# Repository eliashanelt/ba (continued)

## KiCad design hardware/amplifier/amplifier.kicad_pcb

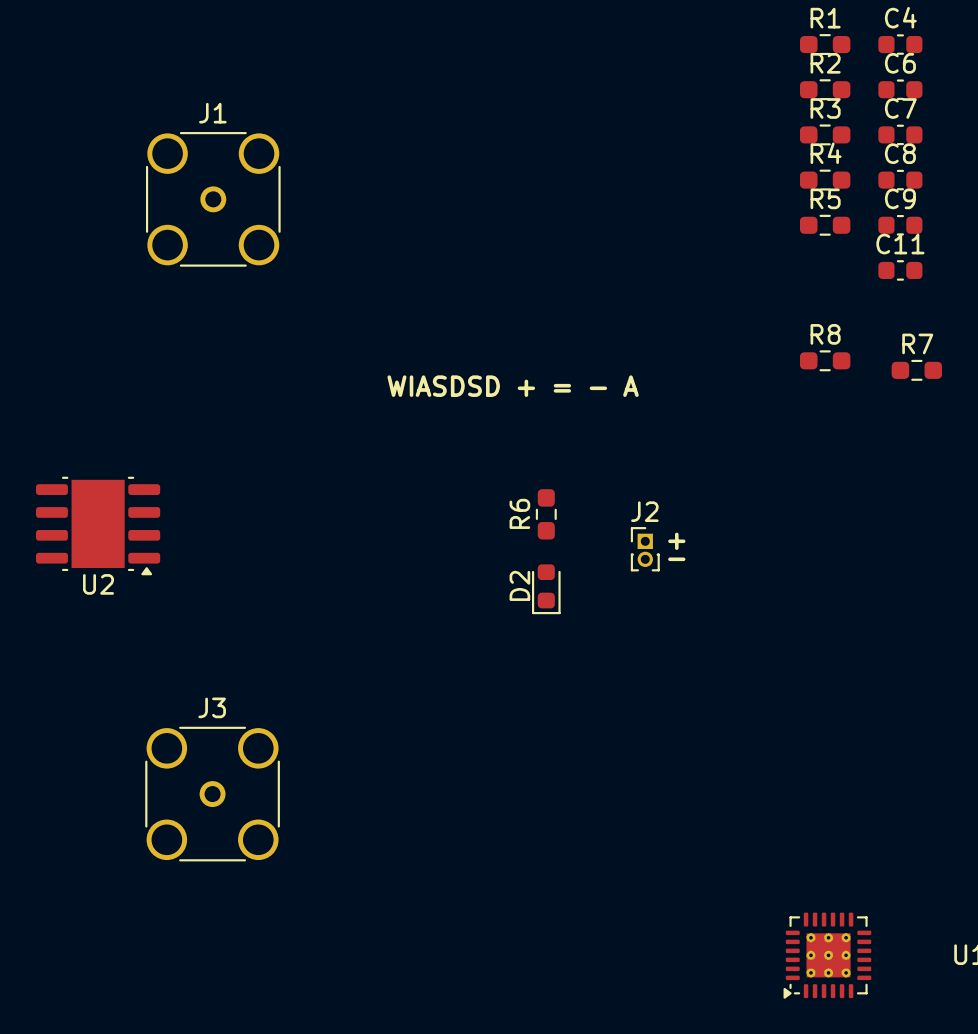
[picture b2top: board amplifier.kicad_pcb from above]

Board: 2 copper layers, 20 parts (0 on the bottom side), 16 nets, no tracks yet.

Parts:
C4, C9: 4.7nF; C_0603_1608Metric
C6: 6.8pF; C_0603_1608Metric
C7, C11: 220nF; C_0603_1608Metric
C8: 100nF; C_0603_1608Metric
D2: LED; LED_0603_1608Metric
J1, J3: Conn_Coaxial; SMA_Amphenol_132134-14_Vertical
J2: Conn_01x02_Socket; PinHeader_1x02_P1.00mm_Vertical
R1: 104.8k; R_0603_1608Metric_Pad0.98x0.95mm_HandSolder
R2: 100; R_0603_1608Metric_Pad0.98x0.95mm_HandSolder
R3: 1.3M; R_0603_1608Metric_Pad0.98x0.95mm_HandSolder
R4: 85.8k; R_0603_1608Metric_Pad0.98x0.95mm_HandSolder
R5: 78.7; R_0603_1608Metric_Pad0.98x0.95mm_HandSolder
R6: 1k; R_0603_1608Metric_Pad0.98x0.95mm_HandSolder
R7: 975k; R_0603_1608Metric_Pad0.98x0.95mm_HandSolder
R8: 698; R_0603_1608Metric_Pad0.98x0.95mm_HandSolder
U1: TPS65131RGE; VQFN-24-1EP_4x4mm_P0.5mm_EP2.45x2.45mm_ThermalVias
U2: THS3491xDDA; Texas_R-PDSO-G8_EP2.95x4.9mm_Mask2.4x3.1mm

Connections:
+5V: J2.1, R6.1
+15V: C6.1, R7.1, U1.23 (VPOS), U2.7 (V+)
-15V: C11.2, R3.2, U1.15 (VNEG), U2.4 (V-)
/IN: J1.1 (In), U2.3 (+)
/OUT: J3.1 (In), R8.2, U2.6
GND: C4.2, C7.2, C8.2, C9.2, D2.1 (K), J1.2 (Ext), J2.2, J3.2 (Ext), R4.2, R5.1, U1.2 (PGND), U1.3 (PGND), U1.19 (AGND), U2.1 (REF)
unnamed: U1.1 (INP), U1.24 (INP)
unnamed: D2.2 (A), R6.2
unnamed: U1.13 (OUTN), U1.14 (OUTN)
unnamed: C9.1, R2.1, U1.5 (INN), U1.6 (INN), U1.7 (BSW)
unnamed: C4.1, U1.18 (CN)
unnamed: C8.1, R2.2, U1.4 (VIN), U1.8 (ENP), U1.9 (PSP), U1.10 (ENN), U1.11 (PSN)
unnamed: C11.1, R1.2, R3.1, U1.16 (FBN)
unnamed: C6.2, R4.1, R7.2, U1.22 (FBP)
unnamed: C7.1, R1.1, U1.17 (VREF)
unnamed: R5.2, R8.1, U2.2 (-)

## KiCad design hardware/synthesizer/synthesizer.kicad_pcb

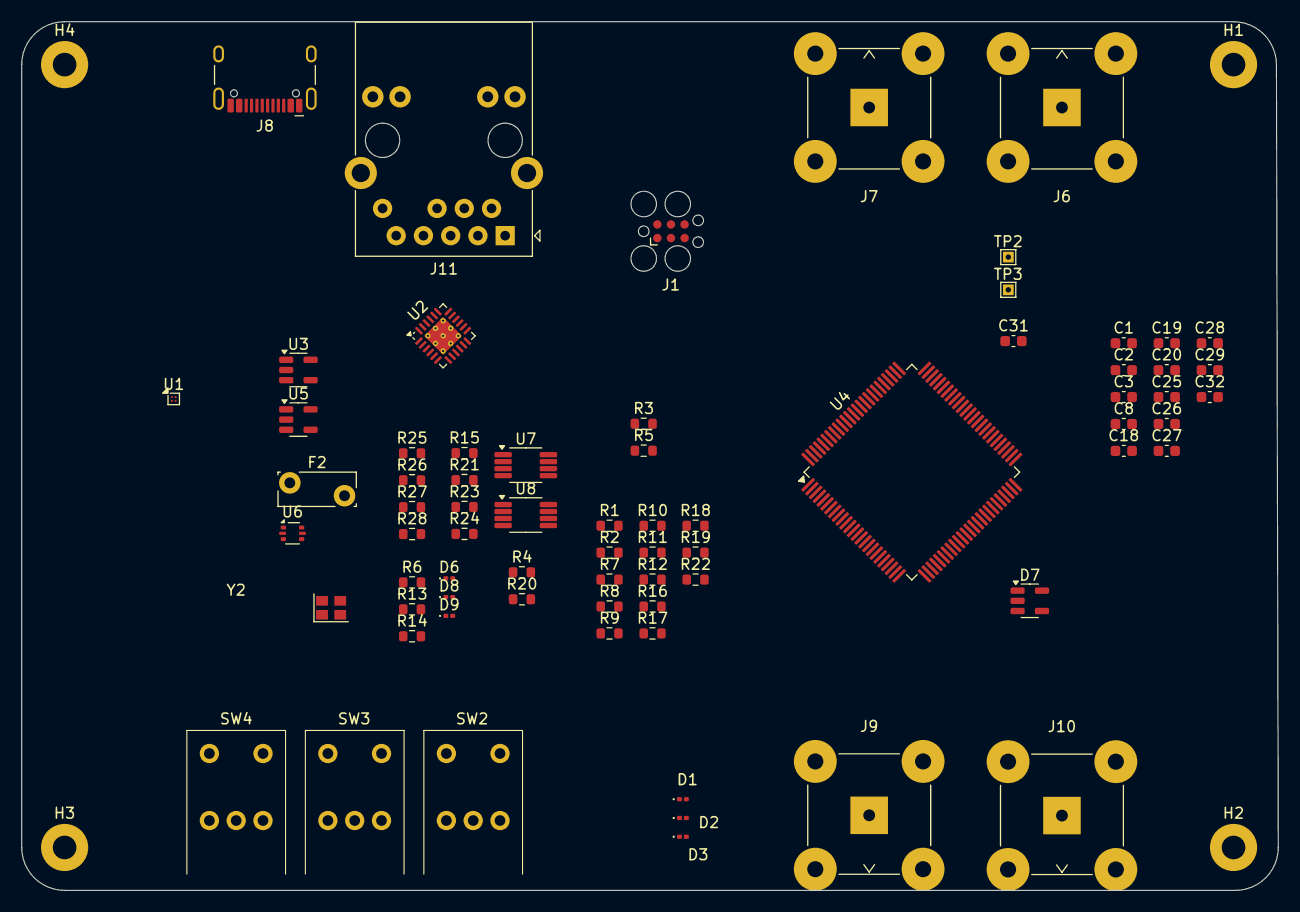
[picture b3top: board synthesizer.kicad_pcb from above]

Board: 2 copper layers, 117.2 x 81.0 mm, 75 parts (0 on the bottom side), 44 nets, no tracks yet.

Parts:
C1, C2, C3, C8, C19, C20, C25, C26, C27, C32: 100n/50V; C_0603_1608Metric
C18: 100n/10V; C_0603_1608Metric
C28, C29: 10p/50V; C_0603_1608Metric
C31: 100nF/10V; C_0603_1608Metric
D1: Yellow; LED_0201_0603Metric
D2, D6: Red; LED_0201_0603Metric
D3: Green; LED_0201_0603Metric
D7: ESDA6V1SC5; SOT-23-5
D8: Blue; LED_0201_0603Metric
D9: Orange; LED_0201_0603Metric
F2: Polyfuse; Fuse_Bourns_MF-RG300
H1, H2, H3, H4: MountingHole; MountingHole_2.2mm_M2_Pad
J1: Conn_ARM_SWD_TagConnect_TC2030; Tag-Connect_TC2030-IDC-FP_2x03_P1.27mm_Vertical
J6: Input 1; BNC_TEConnectivity_1478035_Horizontal
J7: Input 2; BNC_TEConnectivity_1478035_Horizontal
J8: USB_C_Receptacle_USB2.0_14P; USB_C_Receptacle_HCTL_HC-TYPE-C-16P-01A
J9: Output 1; BNC_TEConnectivity_1478035_Horizontal
J10: Output 2; BNC_TEConnectivity_1478035_Horizontal
J11: RJ45_Abracon_ARJP11A-MASA-B-A-EMU2; RJ45_Abracon_ARJP11A-MA_Horizontal
R1, R2, R6, R13, R14, R17: 1k; R_0603_1608Metric
R3, R5: 5.1k; R_0603_1608Metric
R4, R20: 470; R_0603_1608Metric
R7, R8, R9, R19: 49.9k; R_0603_1608Metric
R10, R11, R18, R21, R22, R25, R28: 10k; R_0603_1608Metric
R12: 5.6k; R_0603_1608Metric
R15, R23, R26: 200k; R_0603_1608Metric
R16: 100k; R_0603_1608Metric
R24: 6.8k; R_0603_1608Metric
R27: 4.7k; R_0603_1608Metric
SW2, SW3, SW4: RotaryEncoder; RotaryEncoder_Bourns_Horizontal_PEC09-2xxxF-Sxxxx
TP2, TP3: TestPoint; TestPoint_THTPad_1.0x1.0mm_Drill0.5mm
U1: MAX40200ANS; WLP-4_0.728x0.728mm_Layout2x2_P0.35mm
U2: LAN8742A; VQFN-24-1EP_4x4mm_P0.5mm_EP2.5x2.5mm_ThermalVias
U3: AP2112K-1.2; SOT-23-5
U4: STM32H723VGT6; LQFP-100_14x14mm_P0.5mm
U5: AP2112K-3.3; SOT-23-5
U6: USBLC6-2P6; SOT-666
U7, U8: OPA196xDGK; VSSOP-8_3x3mm_P0.65mm
Y2: SG-210STF; Oscillator_SMD_SeikoEpson_SG210-4Pin_2.5x2.0mm

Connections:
+0.5V: R24.1, R27.2, R28.1
+1.2V: R14.1, R27.1, TP3.1, U2.6 (VDDCR), U3.5 (VOUT)
+3.3V: C1.1, C2.1, C3.1, C19.1, C20.1, C25.1, C26.1, C27.1, C31.1, C32.1, J1.1 (VCC), J11.4 (TCT), J11.5 (RCT), R6.1, R7.1, R8.1, R9.1, R10.1, R16.1, R19.1, SW2.A, SW3.A, SW4.A, TP2.1, U2.1 (VDD2A), U2.9 (VDDIO), U2.19 (VDD1A), U4.6 (VBAT), U4.11 (VDD), U4.21 (VDDA), U4.27 (VDD), U4.50 (VDD), U4.75 (VDD), U4.100 (VDD), U5.5 (VOUT), Y2.1 (~ST), Y2.4 (Vcc)
+5V: R13.2, U1.A2 (OUT), U3.1 (VIN), U3.3 (EN), U5.1 (VIN), U5.3 (EN)
-12V: U7.4 (V-), U8.4 (V-)
/Clocks/25MHz: U2.5 (XTAL1/CLKIN), Y2.3 (OUT)
/Coxial Connectors/OUT_1: J9.1 (In), R15.2, U7.6
/Ethernet Jack/LED1: J11.14, R4.1
/Microcontroller/LED1: R17.1, U4.34 (PB0)
/Microcontroller/LED2: R1.1, U4.35 (PB1)
/Microcontroller/LED3: R2.1, U4.36 (PB2)
/Microcontroller/RST_ETH: R16.2, U2.15 (~RST)
/Microcontroller/RX_N: R19.2, U2.22 (RXN)
/Microcontroller/RX_P: R7.2, U2.23 (RXP)
/Microcontroller/SWCLK: D7.4 (K), J1.4 (SWCLK), U4.76 (PA14(JTCK)
/Microcontroller/SWDIO: D7.3 (K), J1.2 (SWDIO), U4.72 (PA13(JTMS)
/Microcontroller/SWD_NRST: C18.1, D7.5 (K), J1.3 (~RESET), U4.14 (NRST)
/Microcontroller/SWO: D7.1 (K), J1.6 (SWO), U4.89 (PB3(JTDO)
/Microcontroller/TX_N: R8.2, U2.20 (TXN)
/Microcontroller/TX_P: R9.2, U2.21 (TXP)
/Microcontroller/USB+: J8.A6 (D+), J8.B6 (D+), U4.71 (PA12), U6.1 (I/O1)
/Microcontroller/USB-: J8.A7 (D-), J8.B7 (D-), U4.70 (PA11), U6.3 (I/O2)
GND: C1.2, C2.2, C3.2, C8.2, C18.2, C19.2, C20.2, C25.2, C26.2, C27.2, C28.2, C29.2, C31.2, C32.2, D1.1 (K), D2.1 (K), D3.1 (K), D6.1 (K), D7.2 (A), D8.1 (K), D9.1 (K), J1.5 (GND), J6.2 (Ext), J7.2 (Ext), J8.A1 (GND), J8.A12 (GND), J8.B1 (GND), J8.B12 (GND), J9.2 (Ext), J10.2 (Ext), J11.7, R3.1, R4.2, R5.1, R11.2, R12.2, R18.2, R20.2, R22.2, R23.1, R24.2, SW2.B, SW3.B, SW4.B, U1.B2 (GND), U2.25 (VSS), U3.2 (GND), U4.10 (VSS), U4.19 (VSSA), U4.26 (VSS), U4.49 (VSS), U4.74 (VSS), U4.99 (VSS), U5.2 (GND), U6.2 (GND), Y2.2 (GND)
unnamed: D1.2 (A), R1.2
unnamed: D2.2 (A), R2.2
unnamed: D3.2 (A), R17.2
unnamed: D6.2 (A), R6.2
unnamed: D8.2 (A), R13.1
unnamed: D9.2 (A), R14.2
unnamed: F2.1, J8.A4 (VBUS), J8.A9 (VBUS), J8.B4 (VBUS), J8.B9 (VBUS)
unnamed: J8.A5 (CC1), R5.2
unnamed: J8.B5 (CC2), R3.2
unnamed: J11.12, R20.1
unnamed: R10.2, U2.3 (LED1/REGOFF)
unnamed: R11.1, U2.2 (LED2/~INTSEL)
unnamed: R12.1, U2.24 (RBIAS)
unnamed: R18.1, U2.10 (RXER/PHYAD0)
unnamed: R22.1, U4.94 (BOOT0)
unnamed: C29.1, U4.8 (PC14)
unnamed: C28.1, U4.9 (PC15)
unnamed: C8.1, U4.20 (VREF+)
unnamed: R21.1, R23.2, U7.3 (+)
unnamed: R15.1, R28.2, U7.2 (-)
VBUS: F2.2, U1.A1 (VDD), U1.B1 (EN), U6.5 (VBUS)

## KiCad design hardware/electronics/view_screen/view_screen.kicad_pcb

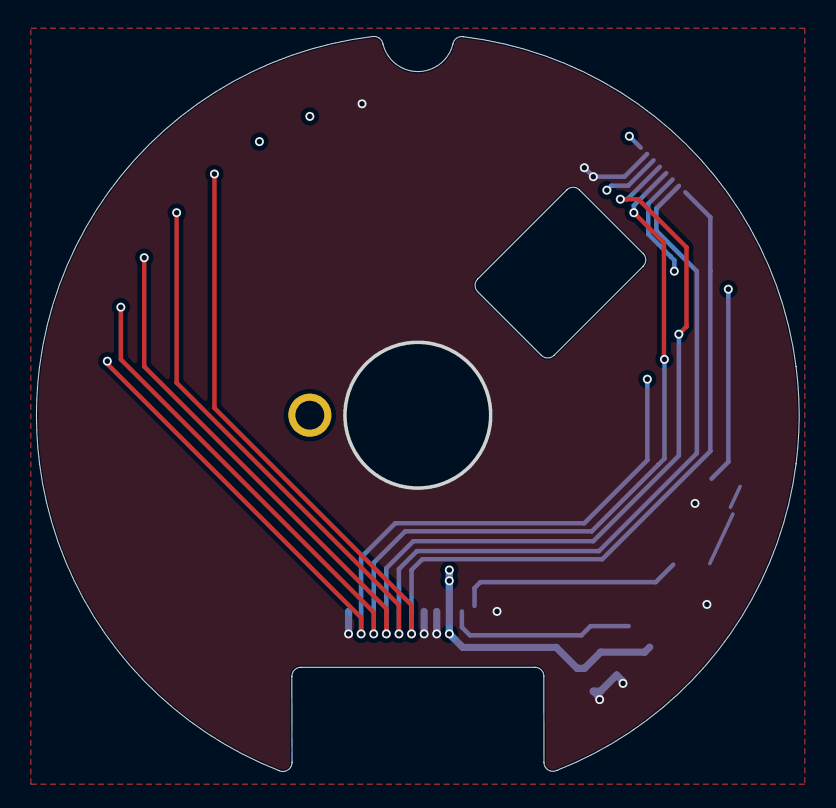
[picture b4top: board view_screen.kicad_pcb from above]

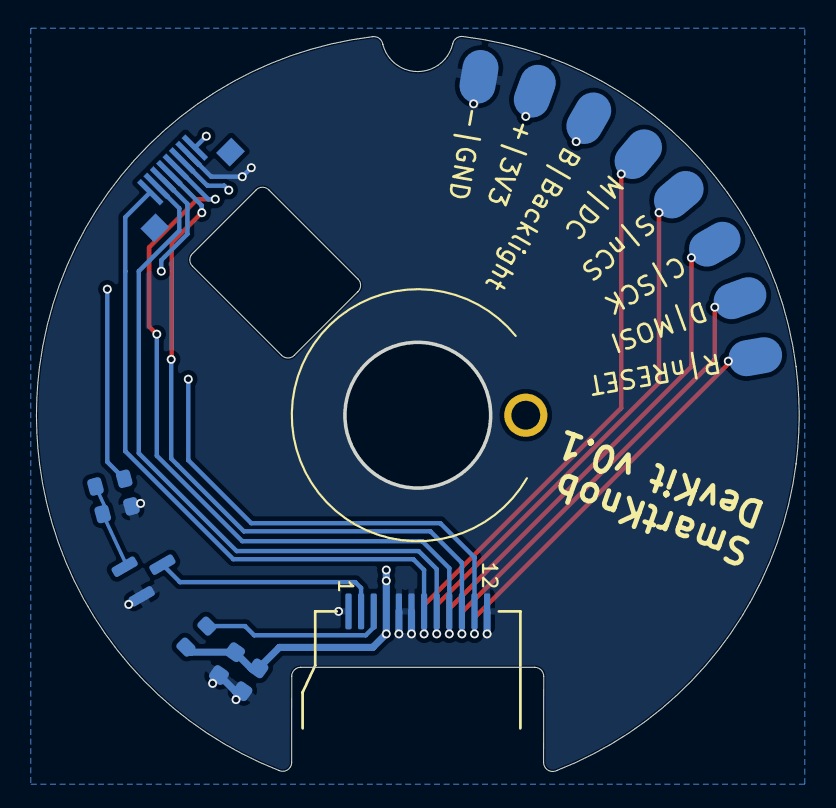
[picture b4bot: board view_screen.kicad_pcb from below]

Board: 4 copper layers, 42.4 x 40.8 mm, 17 parts (16 on the bottom side), 11 nets.

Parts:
C1: 22uF; C_0603_1608Metric
C2: 0.1uF; C_0603_1608Metric
H1: AlignmentHole; AlignmentHole_1.6
J2: GC9A01; GC9A01Round1.28
J6: LCD - FPC; Amphenol FCI FPC 8 pin 0.5 pitch
Q1: 2N7002; SOT-23
R1: 10k; R_0603_1608Metric
R2: 22R; R_0603_1608Metric
R3: 1M; R_0603_1608Metric
TP1: S|nCS; test_point_connectivity
TP2: C|SCK; test_point_connectivity
TP3: D|MOSI; test_point_connectivity
TP4: R|nRESET; test_point_connectivity
TP5: -|GND; test_point_connectivity
TP6: +|3V3; test_point_connectivity
TP7: B|Backlight; test_point_connectivity
TP8: M|DC; test_point_connectivity

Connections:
/BACKLIGHT_EN: J6.3, R1.1, TP7.1
/DC: J2.7, J6.1, TP8.1
/LEDA: J2.3, R2.2
/LEDK: J2.2, Q1.3 (D)
/MOSI: J2.10, J6.4, TP3.1
/SCK: J2.9, J6.5, TP2.1
/VDD: C1.1, C2.1, J2.4, J6.8, R2.1, TP6.1
/nCS: J2.8, J6.2, TP1.1
/nRESET: J2.11, J6.6, TP4.1
GND: C1.2, C2.2, J2.1, J2.5, J2.6, J2.12, J6.7, Q1.2 (S), R3.2, TP5.1
unnamed: Q1.1 (G), R1.2, R3.1

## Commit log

2025-02-20 work on progres report cw8
2025-02-20 structering of the progress report
2025-02-20 try programming the protenta h7 with rust
2025-02-21 add readme
2025-02-21 upadted title
2025-02-21 create kicadV9 project, carry on cw8 report
2025-02-21 further improved progress report
2025-02-22 start working on synthesizer-pcb
2025-02-23 add jtag connector + continue cw8 report
2025-02-24 add ethernet to synthesizer
2025-02-25 improve report a bit
2025-02-27 created slides for cw8, split schematics
2025-02-27 start connecting sheets
2025-02-28 work on hardware
2025-02-28 update synthesizer
2025-02-28 finish ethernet jack
2025-03-03 clean up synthesizer schematics
2025-03-03 add logo to every sheet
2025-03-04 work on synthesizer schematics - add HSE and LSE oscillators
2025-03-04 add dac test
2025-03-04 first working portenta h7 follower
2025-03-25 further improvements
2025-03-31 improved pcb design
2025-05-04 add a lot of new stuff
2025-05-04 fixed lcd screen
2025-05-05 improved button controller
2025-05-07 add amplifier design
2025-05-12 add smartknob for esp32s3
2025-05-13 add smartknob code
2025-05-13 add led ring functionality
2025-05-13 add spi and i2c
2025-05-13 first non working impl for hal sensor
2025-05-13 working hal sensor
2025-05-13 add hx711 driver
2025-05-15 add motor controller
2025-05-27 add fpga project + commander cody
2025-06-09 make led follow motor orientation
2025-06-09 add press bahivior
2025-06-09 start motor controls
2025-06-09 add foc
2025-06-10 start implementing motor calibration
2025-06-10 add motor calibration
2025-06-10 add more calibration impl
2025-06-10 start implementing bldcmotordriver
2025-06-10 continue impl of foc controller
2025-06-10 improved pid controller
2025-06-10 split of led ring
2025-06-10 start adding strain gauge task
2025-06-10 impl motor task
2025-06-11 move led ring
2025-06-11 organize led_ring
2025-06-11 remove comments in main
2025-06-11 organize project
2025-06-11 add motor_angle task
2025-06-12 reorganizing
2025-06-13 continue further with motor control impl
2025-06-13 continue implementing foc control
2025-06-13 continue implementing foc
2025-06-13 add open loop functions
2025-06-13 add more features
2025-06-13 move calibrate function
2025-06-16 work on bldc driver
2025-06-16 almost done impl bldc motor driver
2025-06-16 continue impl motor
2025-06-16 on press haptic feedback
2025-06-19 add new fpga project
2025-06-23 add spi logic to redpitaya
2025-06-23 add first status info to it
2025-06-23 add redpitaya example
2025-06-24 add spi communication
2025-06-30 add bash upload script to fpga
2025-06-30 working frequency counter
2025-07-01 add fpga flash instructions
2025-07-01 pass through working
2025-07-01 another push
2025-07-01 working signal limit
2025-07-01 add graph drawing
2025-07-04 redpitaya update
2025-07-08 add voltage readout
2025-07-09 freq to voltage level works
2025-07-09 add web interface for redpitaya
2025-07-09 add web control interface
2025-07-09 add web dashboard
2025-07-09 improved web interface
2025-07-09 web interface upgrade
2025-07-09 improvement web interface
2025-07-09 made input fields bigger
2025-07-09 added footer
2025-07-10 add wave preview
2025-07-10 add lv and hv mode to dashboard
2025-07-10 add gain and limits
2025-07-10 fixed limits
2025-07-10 add vp and vpp readout
2025-07-10 modified dashboard
2025-07-10 removed regular status message
2025-07-10 update dashboard
2025-07-10 implemented pressure controller
2025-07-11 cleaned up project
2025-07-11 voltage level fix
